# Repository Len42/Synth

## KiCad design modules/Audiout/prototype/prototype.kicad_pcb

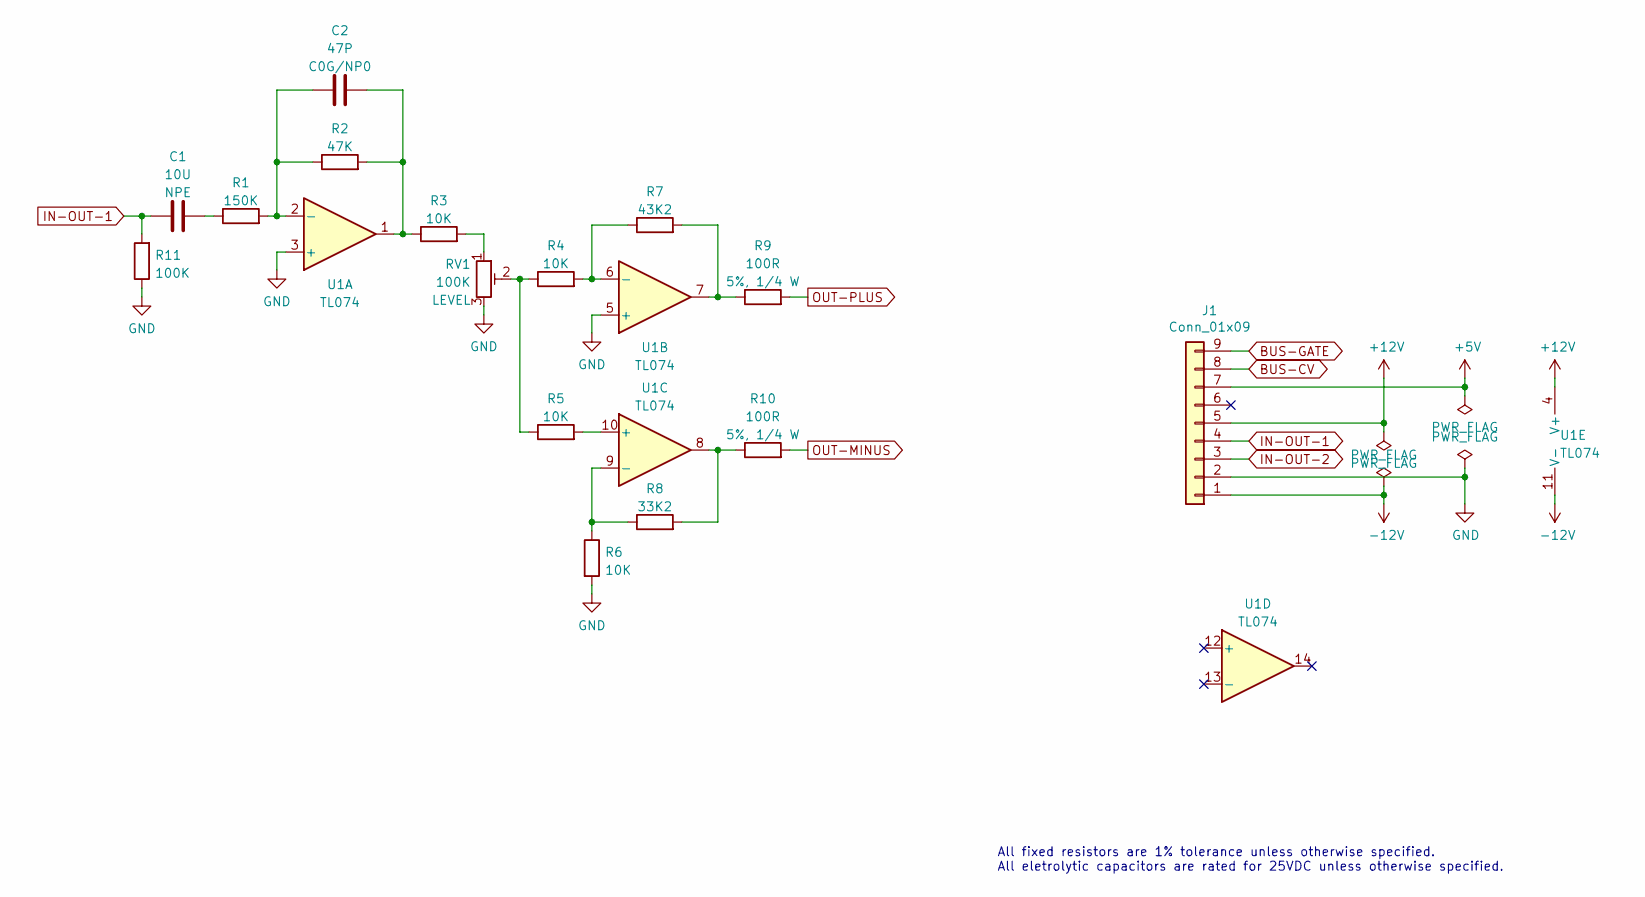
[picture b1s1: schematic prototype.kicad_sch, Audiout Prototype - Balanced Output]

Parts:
C1: 10U; C_Radial_D5.0mm_H5.0mm_P2.50mm; ManufacturerPartNum ECE-A1EN100UI
C2: 47P; C_Disc_D5.0mm_W2.5mm_P2.50mm
J1: Conn_01x09; PinHeader_1x09_P2.54mm_Vertical
R1: 150K; R_Axial_DIN0207_L6.3mm_D2.5mm_P7.62mm_Horizontal; ManufacturerPartNum MFR-12*
R2: 47K; SB_Gen_1; ManufacturerPartNum MFR-12*
R3, R4, R5: 10K; R_Axial_DIN0207_L6.3mm_D2.5mm_P7.62mm_Horizontal; ManufacturerPartNum MFR-12*
R6: 10K; SB_Gen_1; ManufacturerPartNum MFR-12*
R7: 43K2; SB_Gen_1; ManufacturerPartNum MFR-12*
R8: 33K2; SB_Gen_1; ManufacturerPartNum MFR-12*
R9, R10: 100R; R_Axial_DIN0207_L6.3mm_D2.5mm_P10.16mm_Horizontal; ManufacturerPartNum CCF071K00JKE36
R11: 100K; SB_Gen_1; ManufacturerPartNum MFR-12*
RV1: 100K; Potentiometer_Bourns_3310R_Top; ManufacturerPartNum 3386*
U1: TL074; DIP-14_W7.62mm; ManufacturerPartNum TL074BCN

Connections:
+5V: J1.7
+12V: J1.5, U1.4 (V+)
-12V: J1.1, U1.11 (V-)
BUS-CV: J1.8
BUS-GATE: J1.9
GND: J1.2, R6.2, R11.1, RV1.3, U1.3 (+), U1.5 (+)
IN-OUT-1: C1.1, J1.4, R11.2
IN-OUT-2: J1.3
unnamed: C1.2, R1.1
unnamed: C2.2, R1.2, R2.1, U1.2 (-)
unnamed: C2.1, R2.2, R3.1, U1.1
unnamed: R3.2, RV1.1
unnamed: R4.1, R5.1, RV1.2
unnamed: R4.2, R7.1, U1.6 (-)
unnamed: R5.2, U1.10 (+)
unnamed: R6.1, R8.1, U1.9 (-)
unnamed: R7.2, R9.1, U1.7
unnamed: R8.2, R10.1, U1.8
OUT-MINUS: R10.2
OUT-PLUS: R9.2

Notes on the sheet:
All fixed resistors are 1% tolerance unless otherwise specified. All eletrolytic capacitors are rated for 25VDC unless otherwise specified.

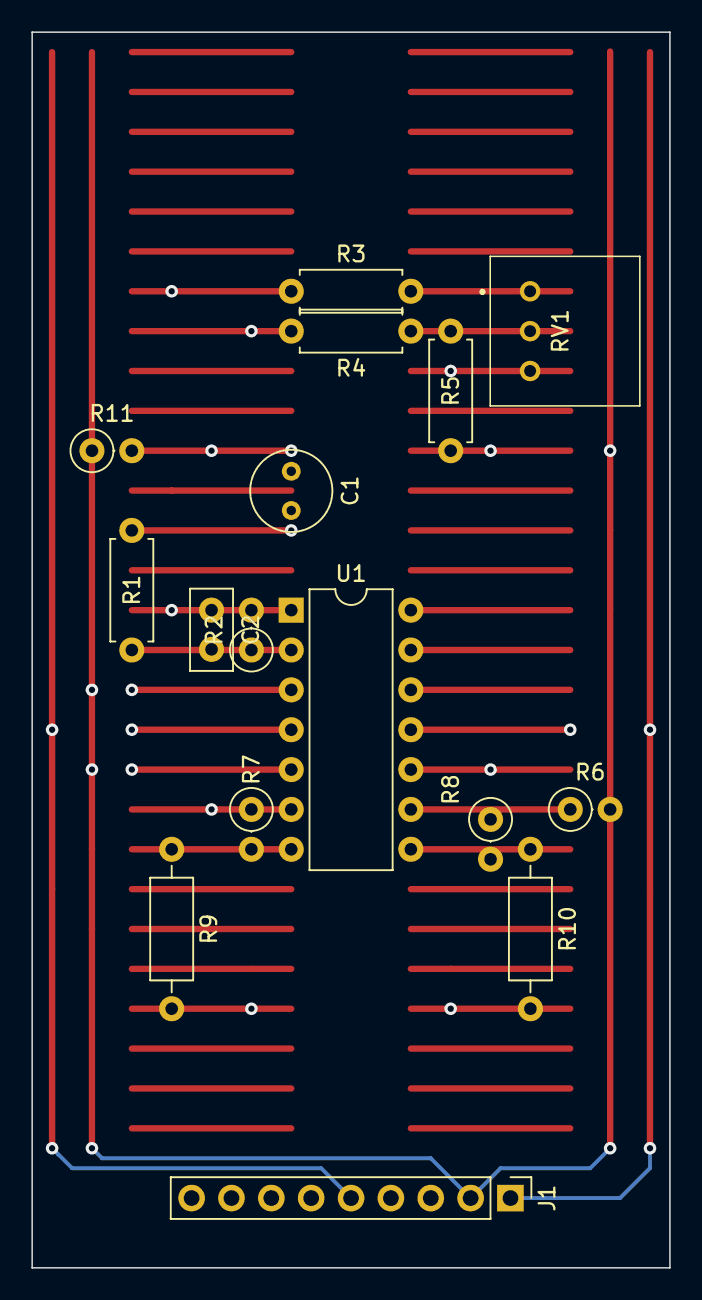
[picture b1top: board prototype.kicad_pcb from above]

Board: 6 copper layers, 40.6 x 78.7 mm, 16 parts (0 on the bottom side), 14 nets.

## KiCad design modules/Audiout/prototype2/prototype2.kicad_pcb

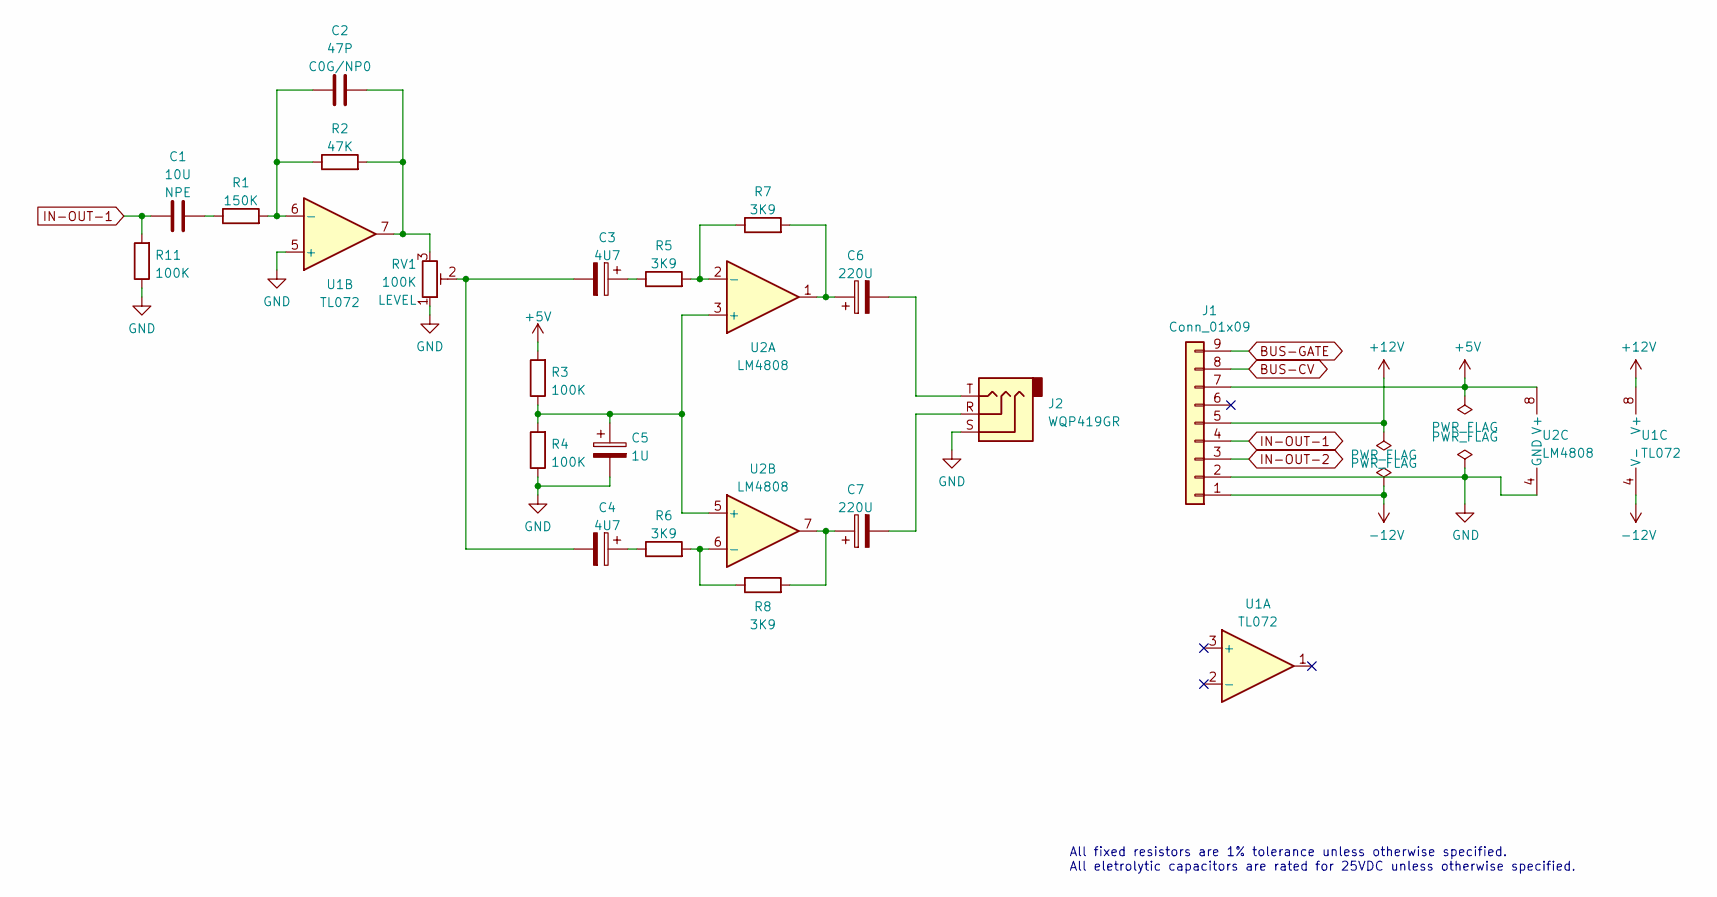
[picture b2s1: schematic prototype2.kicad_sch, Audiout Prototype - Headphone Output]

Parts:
C1: 10U; C_Radial_D5.0mm_H5.0mm_P2.50mm; ManufacturerPartNum ECE-A1EN100UI
C2: 47P; C_Disc_D5.0mm_W2.5mm_P2.50mm
C3, C4: 4U7; CP_Radial_D4.0mm_P2.50mm
C5: 1U; CP_Radial_D4.0mm_P2.50mm
C6, C7: 220U; CP_Radial_D8.0mm_P5.00mm
J1: Conn_01x09; PinHeader_1x09_P2.54mm_Vertical
J2: WQP419GR; Jack_3.5mm_QingPu_WQP-PJ366ST_Vertical; ManufacturerPartNum PJ366ST / WQP419GR
R1: 150K; R_Axial_DIN0207_L6.3mm_D2.5mm_P7.62mm_Horizontal; ManufacturerPartNum MFR-12*
R2: 47K; SB_Gen_1; ManufacturerPartNum MFR-12*
R3, R4, R11: 100K; SB_Gen_1; ManufacturerPartNum MFR-12*
R5, R6, R7, R8: 3K9; R_Axial_DIN0207_L6.3mm_D2.5mm_P7.62mm_Horizontal; ManufacturerPartNum MFR-12*
RV1: 100K; Potentiometer_Bourns_3310R_Top; ManufacturerPartNum 3386*
U1: TL072; DIP-8_W7.62mm; ManufacturerPartNum TL072BCP
U2: LM4808; Breakout_DIP-8_W7.62mm

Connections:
+5V: J1.7, R3.2, U2.8 (V+)
+12V: J1.5, U1.8 (V+)
-12V: J1.1, U1.4 (V-)
BUS-CV: J1.8
BUS-GATE: J1.9
GND: C5.2, J1.2, J2.S, R4.1, R11.1, RV1.1, U1.5 (+), U2.4 (GND)
IN-OUT-1: C1.1, J1.4, R11.2
IN-OUT-2: J1.3
unnamed: C1.2, R1.1
unnamed: C2.1, R2.2, RV1.3, U1.7
unnamed: C2.2, R1.2, R2.1, U1.6 (-)
unnamed: C3.1, R5.1
unnamed: C3.2, C4.2, RV1.2
unnamed: C4.1, R6.1
unnamed: C5.1, R3.1, R4.2, U2.3 (+), U2.5 (+)
unnamed: C6.1, R7.2, U2.1
unnamed: C6.2, J2.T
unnamed: C7.1, R8.2, U2.7
unnamed: C7.2, J2.R
unnamed: R5.2, R7.1, U2.2 (-)
unnamed: R6.2, R8.1, U2.6 (-)

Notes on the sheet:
All fixed resistors are 1% tolerance unless otherwise specified. All eletrolytic capacitors are rated for 25VDC unless otherwise specified.

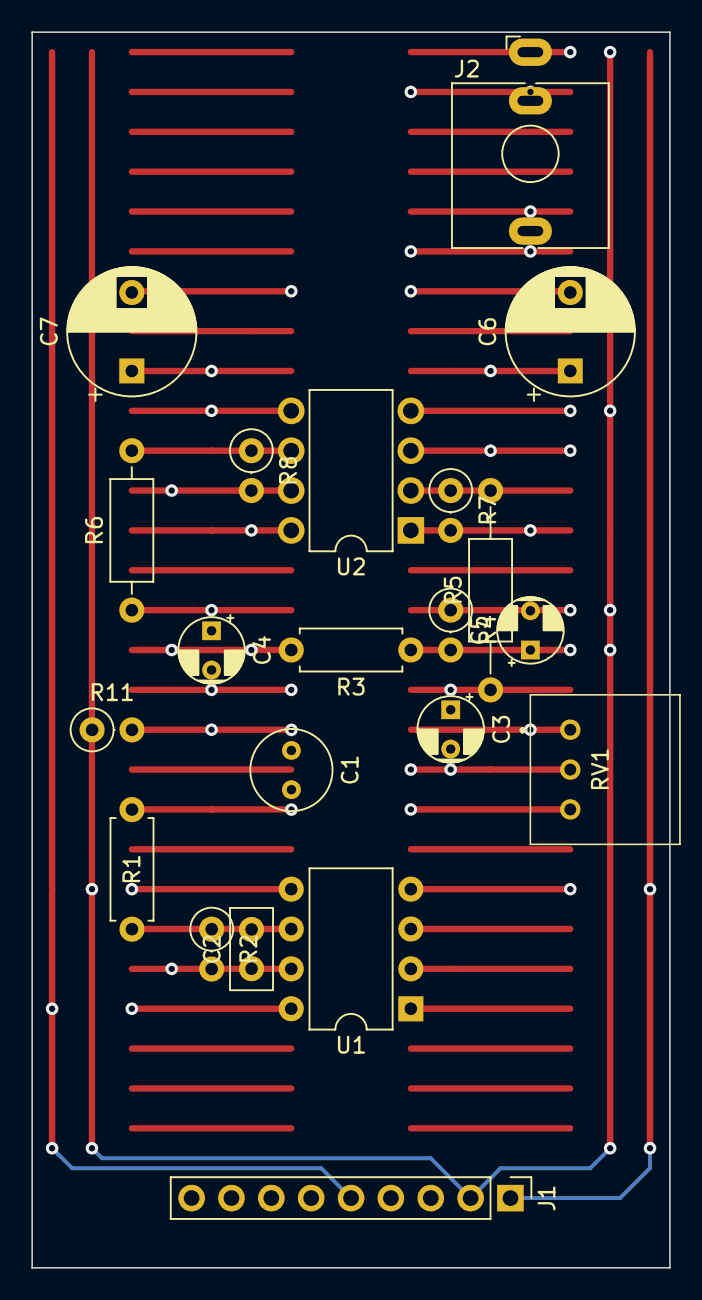
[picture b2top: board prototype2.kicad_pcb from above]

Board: 6 copper layers, 40.6 x 78.7 mm, 21 parts (0 on the bottom side), 18 nets.

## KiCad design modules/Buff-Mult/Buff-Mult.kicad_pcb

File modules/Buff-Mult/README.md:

# Buffered Multiple

## 4HP Eurorack Module

### Features
- Two 1:3 channels - each channel copies an input signal to three outputs
- Input of channel 1 is normalled to channel 2, making a 1:6 multiple when only one input is used
- Outputs are buffered so that they don't affect each other, unlike a passive multiple
- Blinking lights show when a signal is active and whether it's a CV or audio signal

### Notes
PCB layouts are provided in KiCad and gerber formats. A PCB layout for a drilled front panel (with no labels) is also included.

The PCBs that I used can be ordered from OSH Park. The designs are here:
- [Controls board](https://oshpark.com/shared_projects/ZccsRBLi)
- [Main board](https://oshpark.com/shared_projects/PCOUsyZn)
- [Front panel](https://oshpark.com/shared_projects/exBVN6kN)

Please note that I am a hobbyist, not a trained electronics engineer. No guarantees!

### Software Used

* [KiCad](https://www.kicad.org/) 6.0.6

<hr /><div><div style="float:left; padding-right:10px;"></div><div style="xfloat:left; padding-left:10px;"><br />© 2022 Len Popp CC BY<br />This work is licensed under a <a rel="license" href="http://creativecommons.org/licenses/by/4.0/">Creative Commons Attribution 4.0 International License</a>.</div></div>

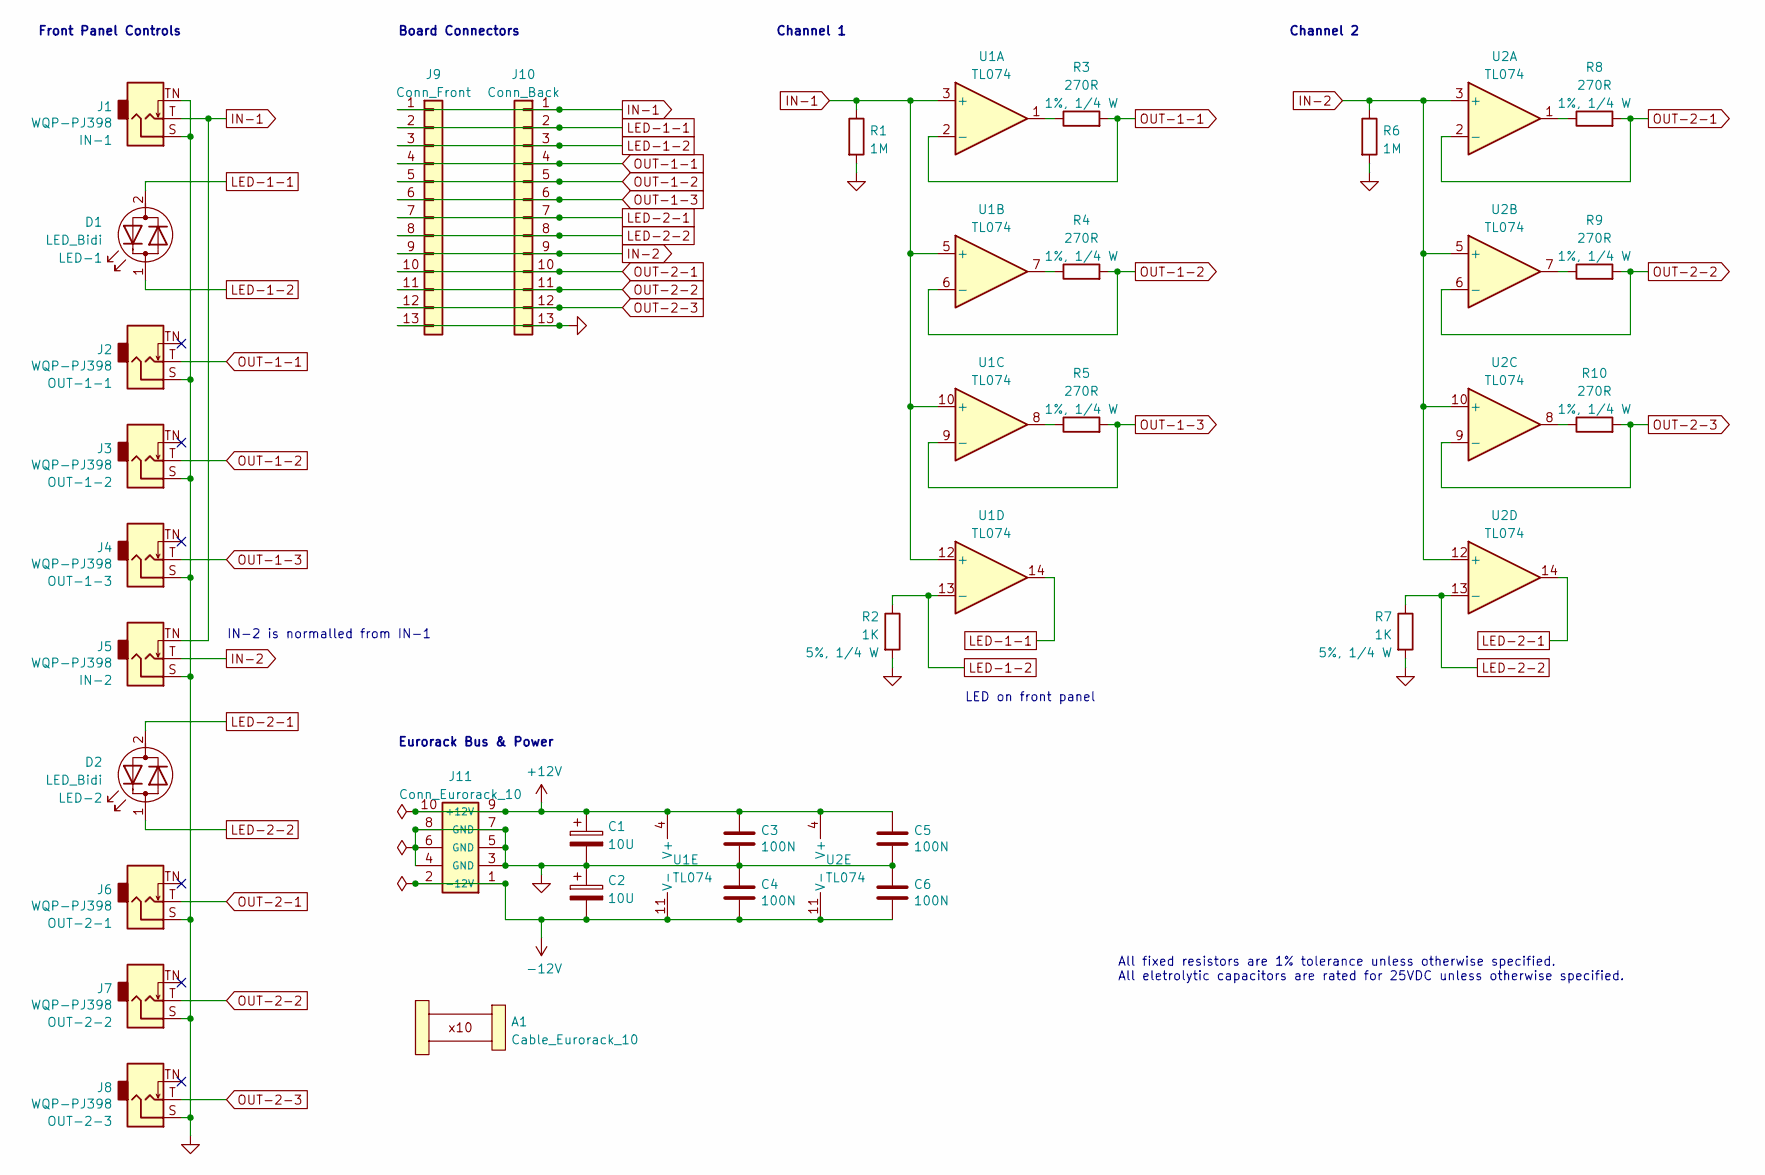
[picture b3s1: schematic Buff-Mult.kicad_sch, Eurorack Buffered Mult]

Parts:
A1: Cable_Eurorack_10; NoFootprint
C1, C2: 10U; CP_Radial_D5.0mm_P2.50mm; ManufacturerPartNum ECE-A1VKS100I
C3, C4, C5, C6: 100N; C_Disc_D5.0mm_W2.5mm_P2.50mm; ManufacturerPartNum FG18X7R1H104KNT06
D1, D2: LED_Bidi; LED_D3.0mm; ManufacturerPartNum WP937GYW
J1, J2, J3, J4, J5, J6, J7, J8: WQP-PJ398; Jack_3.5mm_QingPu_WQP-PJ398SM_Vertical; ManufacturerPartNum PJ398SM / WQP518MA
J9: Conn_Front; PinSocket_1x13_P2.54mm_Vertical
J10: Conn_Back; PinHeader_1x13_P2.54mm_Horizontal
J11: Conn_Eurorack_10; IDC-Header-Eurorack-10-TH; ManufacturerPartNum 61201021621
R1, R6: 1M; R_Axial_DIN0207_L6.3mm_D2.5mm_P7.62mm_Horizontal; ManufacturerPartNum MFR-12FTE52-1M
R2, R7: 1K; R_Axial_DIN0207_L6.3mm_D2.5mm_P10.16mm_Horizontal; ManufacturerPartNum CCF071K00JKE36
R3, R4, R5, R8, R9, R10: 270R; R_Axial_DIN0207_L6.3mm_D2.5mm_P10.16mm_Horizontal; ManufacturerPartNum MFR-25FRF52-270R
U1, U2: TL074; DIP-14_W7.62mm; ManufacturerPartNum TL074BCN

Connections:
+12V: C1.1, C3.1, C5.1, J11.9 (+12V), J11.10, U1.4 (V+), U2.4 (V+)
-12V: C2.2, C4.2, C6.2, J11.1 (-12V), J11.2, U1.11 (V-), U2.11 (V-)
GND: C1.2, C2.1, C3.2, C4.1, C5.2, C6.1, J1.S, J1.TN, J2.S, J3.S, J4.S, J5.S, J6.S, J7.S, J8.S, J9.13, J10.13, J11.3 (GND), J11.4, J11.5 (GND), J11.6, J11.7 (GND), J11.8, R1.2, R2.2, R6.2, R7.2
IN-1: J1.T, J5.TN, J9.1, J10.1, R1.1, U1.3 (+), U1.5 (+), U1.10 (+), U1.12 (+)
IN-2: J5.T, J9.9, J10.9, R6.1, U2.3 (+), U2.5 (+), U2.10 (+), U2.12 (+)
LED-1-1: D1.2, J9.2, J10.2, U1.14
LED-1-2: D1.1, J9.3, J10.3, R2.1, U1.13 (-)
LED-2-1: D2.2, J9.7, J10.7, U2.14
LED-2-2: D2.1, J9.8, J10.8, R7.1, U2.13 (-)
unnamed: R3.1, U1.1
unnamed: R4.1, U1.7
unnamed: R5.1, U1.8
unnamed: R8.1, U2.1
unnamed: R9.1, U2.7
unnamed: R10.1, U2.8
OUT-1-1: J2.T, J9.4, J10.4, R3.2, U1.2 (-)
OUT-1-2: J3.T, J9.5, J10.5, R4.2, U1.6 (-)
OUT-1-3: J4.T, J9.6, J10.6, R5.2, U1.9 (-)
OUT-2-1: J6.T, J9.10, J10.10, R8.2, U2.2 (-)
OUT-2-2: J7.T, J9.11, J10.11, R9.2, U2.6 (-)
OUT-2-3: J8.T, J9.12, J10.12, R10.2, U2.9 (-)

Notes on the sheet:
All fixed resistors are 1% tolerance unless otherwise specified. All eletrolytic capacitors are rated for 25VDC unless otherwise specified.
Eurorack Bus & Power
Channel 1
Board Connectors
Channel 2
IN-2 is normalled from IN-1
LED on front panel
Front Panel Controls

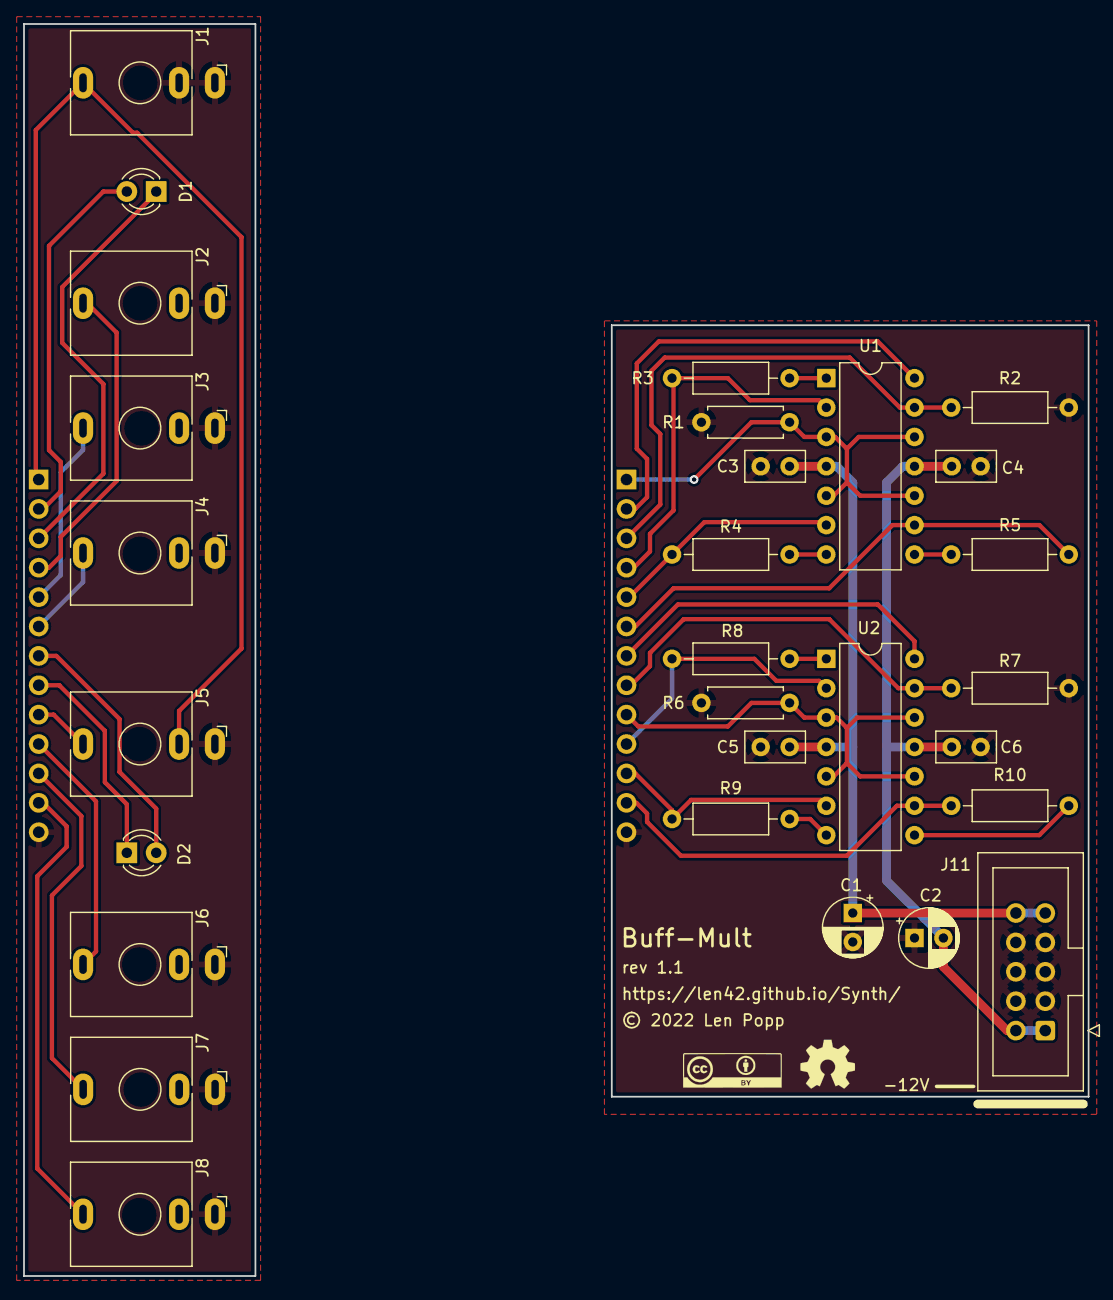
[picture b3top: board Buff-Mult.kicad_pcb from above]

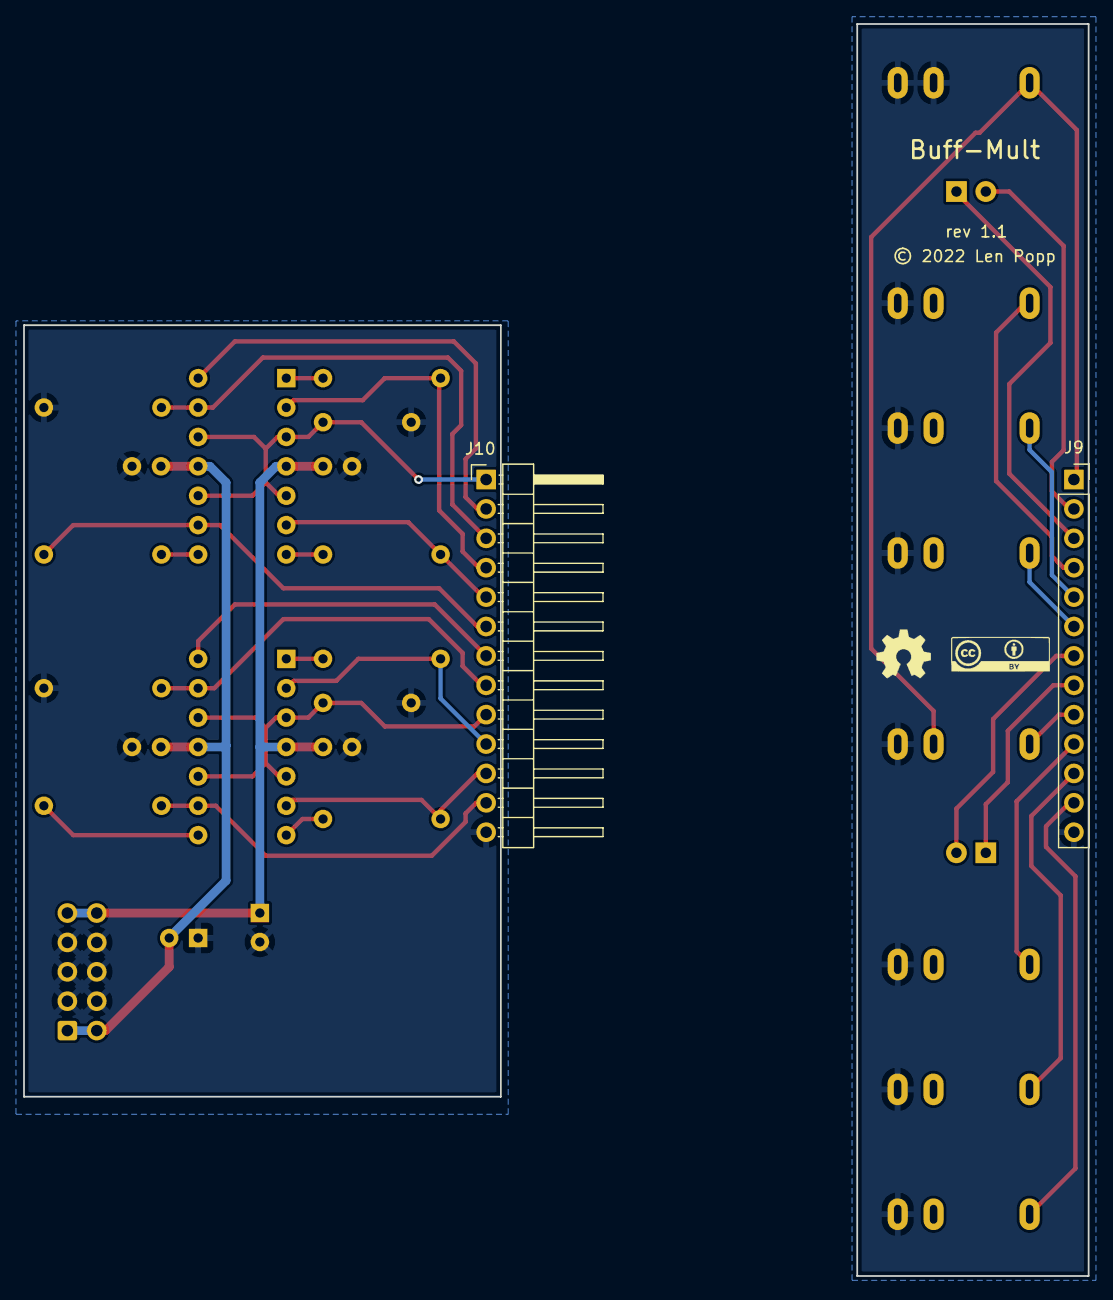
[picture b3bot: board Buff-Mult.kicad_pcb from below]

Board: 2 copper layers, 92.0 x 108.2 mm, 35 parts (4 on the bottom side), 21 nets.

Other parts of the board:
G1, G2: Logo_CC_BY
G3, G4: Logo_OSHW

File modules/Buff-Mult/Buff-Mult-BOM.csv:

Ref,Qty,Value,Value2,Note,Description,Datasheet,Manufacturer,ManuPartNum,Distributor1,DistributorPartNum1,DistributorPartLink1,Distributor2,DistributorPartNum2,DistributorPartLink2,Distributor3,DistributorPartNum3,DistributorPartLink3
"A1","1","Cable_Eurorack_10","","Length as required","Eurorack 16-10 pin power cable","","","","Thonk","","https://www.thonk.co.uk/shop/eurorack-power-cables/","SynthCube","","https://synthcube.com/cart/eurorack-ribbon-power-cables","Modular Addict","","https://modularaddict.com/parts/eurorack-power-cables-1"
"C1 C2","2","10U","35 VDC","12 V decoupling","Capacitor - Electrolytic - 12 V decoupling","https://www.mouser.ca/datasheet/2/315/ABA0000C1059-947582.pdf","Panasonic","ECE-A1VKS100I","Mouser","667-ECE-A1VKS100I","https://www.mouser.ca/ProductDetail/667-ECE-A1VKS100I","Thonk","Group_Eurorack_DIY_Essential","https://www.thonk.co.uk/shop/eurorack-diy-essentials/","","",""
"C3 C4 C5 C6","4","100N","","IC decoupling","Capacitor - Ceramic - IC decoupling","https://product.tdk.com/system/files/dam/doc/product/capacit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","TDK","FG18X7R1H104KNT06","Mouser","810-FG18X7R1H104KNT6","https://www.mouser.ca/ProductDetail/810-FG18X7R1H104KNT6","","","","","",""
"D1 D2","2","LED_Bidi","","","Dual LED, red and green, common cathode on pin 2","https://www.mouser.ca/datasheet/2/216/WP937GYW-49419.pdf","Kingbright","WP937GYW","Mouser","604-WP937GYW","https://www.mouser.ca/ProductDetail/Kingbright/WP937GYW?qs=p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","","","","","",""
"J1 J2 J3 J4 J5 J6 J7 J8","8","WQP-PJ398","","","Audio Jack, 2 Poles (Mono / TS), Switched T Pole (Normalling), QingPu / Thonkiconn","http://www.qingpu-electronics.com/en/products/WQP-PJ398SM-362.html","QingPu / Thonk","PJ398SM / WQP518MA","Thonk","PJ398SM","https://www.thonk.co.uk/shop/thonkiconn/","SynthCube","WQP518MA","https://synthcube.com/cart/3-5mm-euro-jacks","Adafruit","4031","https://www.adafruit.com/product/4031"
"J9","1","Conn_Front","","","Generic connector, single row, 01x13, script generated (kicad-library-utils/schlib/autogen/connector/)","https://cdn-shop.adafruit.com/datasheets/00548.pdf","","","Adafruit","598","https://www.adafruit.com/product/598","Mouser","710-61303211821","https://www.mouser.ca/ProductDetail/Wurth-Elektronik/6130321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","","",""
"J10","1","Conn_Back","","","Generic connector, single row, 01x13, script generated (kicad-library-utils/schlib/autogen/connector/)","https://www.amphenol-icc.com/media/wysiwyg/files/documentati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","","","Adafruit","1540","https://www.adafruit.com/product/1540","Mouser","649-1012937993601BLF","https://www.mouser.ca/ProductDetail/Amphenol-FCI/10129379-93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","","",""
"J11","1","Conn_Eurorack_10","","","Eurorack 10-pin board power connector","https://www.mouser.ca/datasheet/2/445/61201021621-1717731.pdf","Wurth Elektronik","61201021621","Mouser","710-61201021621","https://www.mouser.ca/ProductDetail/Wurth-Elektronik/6120102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","Thonk","523-G821EU210AAL10Y","https://www.thonk.co.uk/shop/eurorack-diy-essentials/","","",""
"R1 R6","2","1M","1%, 1/6 W","","Resistor","https://www.mouser.ca/datasheet/2/447/Yageo_LR_MFR_1-1714151.pdf","YAGEO","MFR-12FTE52-1M","Mouser","603-MFR-12FTE52-1M","https://www.mouser.ca/ProductDetail/603-MFR-12FTE52-1M","","","","","",""
"R2 R7","2","1K","5%, 1/4 W","","Resistor","https://www.mouser.ca/datasheet/2/427/ccf07-1762725.pdf","Vishay / Dale","CCF071K00JKE36","Mouser","71-CCF071K00JKE36","https://www.mouser.ca/ProductDetail/Vishay-Dale/CCF071K00JKE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","","","","","",""
"R3 R4 R5 R8 R9 R10","6","270R","1%, 1/4 W","Output limiting","Resistor","https://www.mouser.ca/datasheet/2/447/Yageo_LR_MFR_1-1714151.pdf","YAGEO","MFR-25FRF52-270R","Mouser","603-MFR-25FRF52-270R","https://www.mouser.ca/ProductDetail/603-MFR-25FRF52-270R","","","","","",""
"U1 U2","2","TL074","","","Quad Low-Noise JFET-Input Operational Amplifiers, DIP-14/SOIC-14","http://www.ti.com/lit/ds/symlink/tl071.pdf","Texas Instruments","TL074BCN","Mouser","595-TL074BCN","https://www.mouser.ca/ProductDetail/?qs=vxEfx8VrU7BHurOY5iQd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","","","","","",""

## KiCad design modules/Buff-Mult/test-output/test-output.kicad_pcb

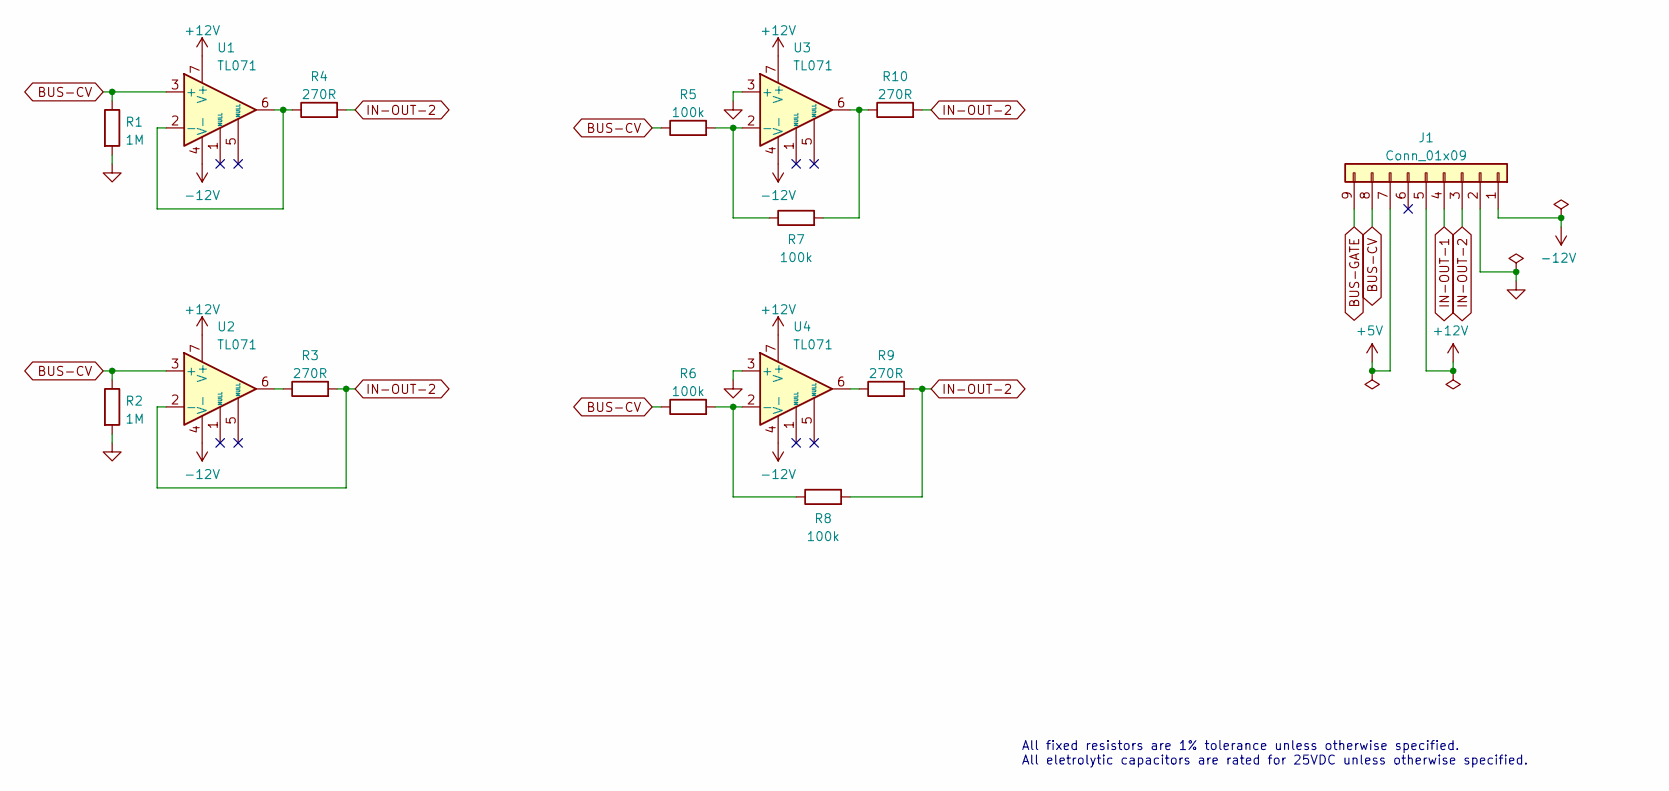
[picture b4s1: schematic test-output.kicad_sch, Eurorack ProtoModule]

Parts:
J1: Conn_01x09; PinHeader_1x09_P2.54mm_Vertical
R1, R2: 1M; R_Axial_DIN0207_L6.3mm_D2.5mm_P7.62mm_Horizontal; ManufacturerPartNum MFR-12*
R3, R4, R9, R10: 270R; R_Axial_DIN0207_L6.3mm_D2.5mm_P7.62mm_Horizontal; ManufacturerPartNum MFR-12*
R5, R6, R7, R8: 100k; R_Axial_DIN0207_L6.3mm_D2.5mm_P7.62mm_Horizontal; ManufacturerPartNum MFR-12*
U1, U2, U3, U4: TL071; DIP-8_W7.62mm; ManufacturerPartNum TL071BCP

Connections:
+5V: J1.7
+12V: J1.5, U1.7 (V+), U2.7 (V+), U3.7 (V+), U4.7 (V+)
-12V: J1.1, U1.4 (V-), U2.4 (V-), U3.4 (V-), U4.4 (V-)
BUS-CV: J1.8, R1.1, R2.1, R5.1, R6.1, U1.3 (+), U2.3 (+)
BUS-GATE: J1.9
GND: J1.2, R1.2, R2.2, U3.3 (+), U4.3 (+)
IN-OUT-1: J1.4
IN-OUT-2: J1.3, R3.2, R4.2, R8.2, R9.2, R10.2, U2.2 (-)
unnamed: R3.1, U2.6
unnamed: R4.1, U1.2 (-), U1.6
unnamed: R5.2, R7.1, U3.2 (-)
unnamed: R6.2, R8.1, U4.2 (-)
unnamed: R9.1, U4.6
unnamed: R7.2, R10.1, U3.6

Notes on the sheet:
All fixed resistors are 1% tolerance unless otherwise specified. All eletrolytic capacitors are rated for 25VDC unless otherwise specified.

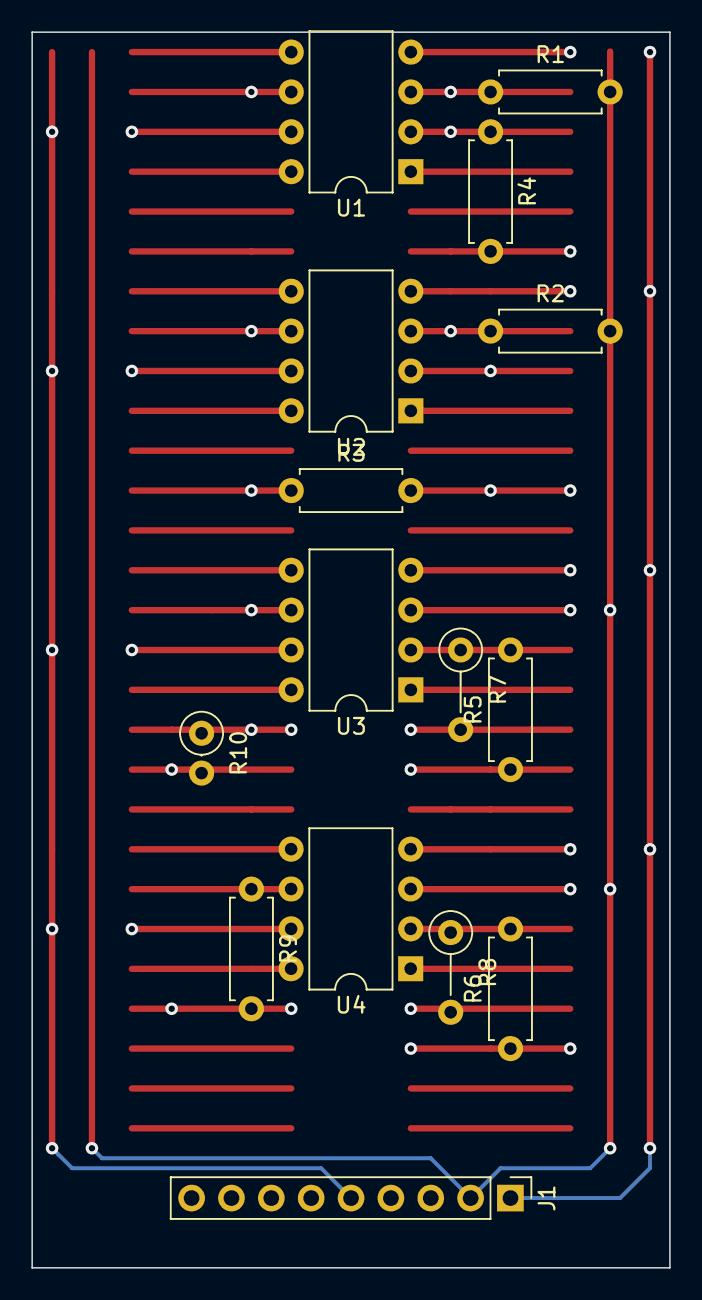
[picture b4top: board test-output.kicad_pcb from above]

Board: 6 copper layers, 40.6 x 78.7 mm, 15 parts (0 on the bottom side), 11 nets.

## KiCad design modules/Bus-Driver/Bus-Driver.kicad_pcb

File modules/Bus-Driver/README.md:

# Bus Driver

## 3HP Eurorack Module

This module sends CV and gate signals to the Eurorack bus, for any modules that pay attention to those bus lines.

### Features
- CV and gate inputs are sent to the corresponding lines on the Eurorack power bus
- Inputs are also copied to output jacks on the front panel
- Bus and front panel outputs are buffered separately
- Inputs are normalled to 0 V, and can be completely disconnected from the bus by a switch

### Notes
This module is only useful if you have other modules that can use the CV & gate signals on the Eurorack bus (such as my [VCO](https://github.com/Len42/Synth/tree/main/modules/VCO-2131) and [envelope](https://github.com/Len42/Synth/tree/main/modules/Envelope2) modules, for example).

The CV and gate inputs could come from a keyboard, or a sequencer, or an [interface module](https://www.expert-sleepers.co.uk/es8.html).

It's important to ensure that this module is the only one in the system that is sending signals to the Eurorack bus CV & gate lines! Several modules may _receive_ those signals, but only one can send them.

There is a switch to disconnect the CV & gate signals from the Eurorack bus.

This module requires a 16-pin Eurorack power cable, but it does not depend on +5V power from the Eurorack system. Note that this module has only a single-row power connector (due to the module being so slim). It can plug into either side of the standard 16-pin cable connector - just make sure to plug in the cable with the red stripe next to the -12 V indication on the module, as always.

PCB layouts are provided in KiCad and gerber formats. A PCB layout for a drilled front panel (with no labels) is also included.

The PCBs that I used can be ordered from OSH Park. The designs are here:
- [Front panel](https://oshpark.com/shared_projects/DCkcxofG)
- [Controls board](https://oshpark.com/shared_projects/zJFNumpm)
- [Main board](https://oshpark.com/shared_projects/tTGp0mmq) (**Note:** This is version 2.0 of the PCB, which works but is not quite as good as the current version.)

Please note that I am a hobbyist, not a trained electronics engineer. No guarantees!

### Software Used

* [KiCad](https://www.kicad.org/) 6.0.6

<hr /><div><div style="float:left; padding-right:10px;"></div><div style="xfloat:left; padding-left:10px;"><br />© 2022 Len Popp CC BY<br />This work is licensed under a <a rel="license" href="http://creativecommons.org/licenses/by/4.0/">Creative Commons Attribution 4.0 International License</a>.</div></div>

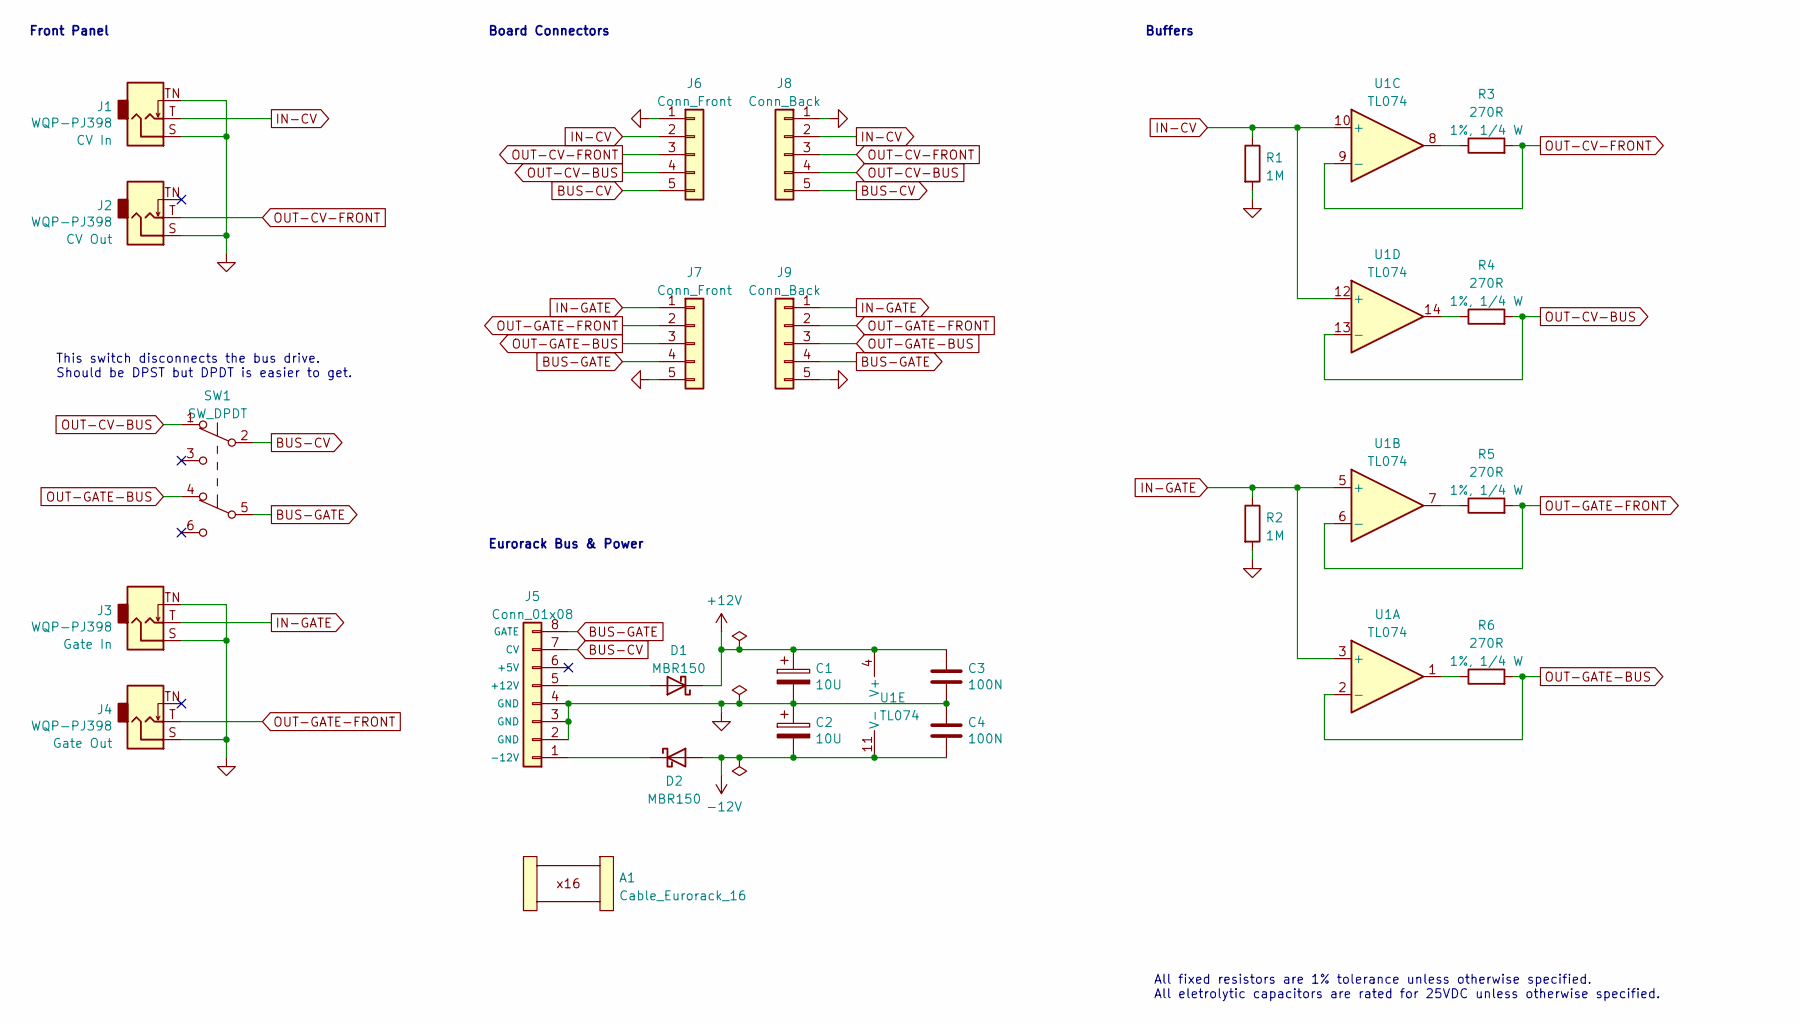
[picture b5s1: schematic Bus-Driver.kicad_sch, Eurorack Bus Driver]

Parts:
A1: Cable_Eurorack_16; NoFootprint
C1, C2: 10U; CP_Radial_D5.0mm_P2.50mm; ManufacturerPartNum ECE-A1VKS100I
C3, C4: 100N; C_Disc_D5.0mm_W2.5mm_P2.50mm; ManufacturerPartNum FG18X7R1H104KNT06
D1, D2: MBR150; D_DO-41_SOD81_P7.62mm_Horizontal; ManufacturerPartNum MBR150RLG
J1, J2, J3, J4: WQP-PJ398; Jack_3.5mm_QingPu_WQP-PJ398SM_Vertical; ManufacturerPartNum PJ398SM / WQP518MA
J5: Conn_01x08; PinHeader-Eurorack-8-TH-RA
J6, J7: Conn_Front; PinSocket_1x05_P2.54mm_Vertical
J8, J9: Conn_Back; PinHeader_1x05_P2.54mm_Horizontal
R1, R2: 1M; R_Axial_DIN0207_L6.3mm_D2.5mm_P7.62mm_Horizontal; ManufacturerPartNum MFR-12*
R3, R4, R5, R6: 270R; R_Axial_DIN0207_L6.3mm_D2.5mm_P10.16mm_Horizontal; ManufacturerPartNum MFR-25FRF52-270R
SW1: SW_DPDT; SW_DPDT_THT_2.54; ManufacturerPartNum 2S1-MDP1-T1-B1-M2QE
U1: TL074; DIP-14_W7.62mm; ManufacturerPartNum TL074BCN

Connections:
+12V: C1.1, C3.1, D1.1 (K), U1.4 (V+)
-12V: C2.2, C4.2, D2.2 (A), U1.11 (V-)
BUS-CV: J5.7 (CV), J6.5, J8.5, SW1.2 (B)
BUS-GATE: J5.8 (GATE), J7.4, J9.4, SW1.5 (B)
GND: C1.2, C2.1, C3.2, C4.1, J1.S, J1.TN, J2.S, J3.S, J3.TN, J4.S, J5.2 (GND), J5.3 (GND), J5.4 (GND), J6.1, J7.5, J8.1, J9.5, R1.2, R2.2
IN-CV: J1.T, J6.2, J8.2, R1.1, U1.10 (+), U1.12 (+)
IN-GATE: J3.T, J7.1, J9.1, R2.1, U1.3 (+), U1.5 (+)
unnamed: D1.2 (A), J5.5 (+12V)
unnamed: D2.1 (K), J5.1 (-12V)
unnamed: R3.1, U1.8
unnamed: R4.1, U1.14
unnamed: R5.1, U1.7
unnamed: R6.1, U1.1
OUT-CV-BUS: J6.4, J8.4, R4.2, SW1.1 (A), U1.13 (-)
OUT-CV-FRONT: J2.T, J6.3, J8.3, R3.2, U1.9 (-)
OUT-GATE-BUS: J7.3, J9.3, R6.2, SW1.4 (A), U1.2 (-)
OUT-GATE-FRONT: J4.T, J7.2, J9.2, R5.2, U1.6 (-)

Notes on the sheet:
All fixed resistors are 1% tolerance unless otherwise specified. All eletrolytic capacitors are rated for 25VDC unless otherwise specified.
Board Connectors
Front Panel
This switch disconnects the bus drive. Should be DPST but DPDT is easier to get.
Eurorack Bus & Power
Buffers

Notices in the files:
modules/Audiout/prototype/prototype.kicad_pcb:
Copyright © 2022 Len Popp CC BY
